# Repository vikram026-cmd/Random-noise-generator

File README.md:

# Random Noise Generator

## Overview
This project presents the design and implementation of a **Random Noise Generator**. The circuit was first simulated using LTspice to analyze noise behavior, and then implemented as a **2-layer PCB using KiCad**.

The project demonstrates the complete workflow from simulation to hardware design.

---

## Features
- Generation of random noise signals  
- Simulation of white noise and pink noise  
- Frequency behavior analysis  
- 2-layer PCB design  
- Compact and practical layout  

---

## Tools Used
- **LTspice** – Circuit simulation  
- **KiCad** – Schematic and PCB design  

---

## Project Workflow

### 1. LTspice Simulation
- Designed and simulated the circuit  
- Observed random signal behavior  
- Verified noise characteristics  

### 2. PCB Design (KiCad)
- Recreated schematic in KiCad  
- Designed a 2-layer PCB  
- Optimized component placement and routing  

---

## Results
- Successfully generated random noise signals in simulation  
- Verified expected noise behavior  
- Designed a functional 2-layer PCB  
- Layout is ready for fabrication  

---

## Applications
- Electronic system testing  
- Audio signal generation  
- Communication systems  

---

## Future Improvements
- Hardware fabrication and testing  
- Adjustable noise control  
- Signal filtering enhancements  

---

## Reference
R. L. Boylestad and L. Nashelsky, *Electronic Devices and Circuit Theory*, 11th ed., Pearson, 2013.

---

## Author
**THANGAVIKRAMAN RAMACHANDRAN**  
B.E. Electronics and Communication Engineering (Pre-Final Year)  

🔗 LinkedIn: https://www.linkedin.com/in/thangavikraman-ramachandran/

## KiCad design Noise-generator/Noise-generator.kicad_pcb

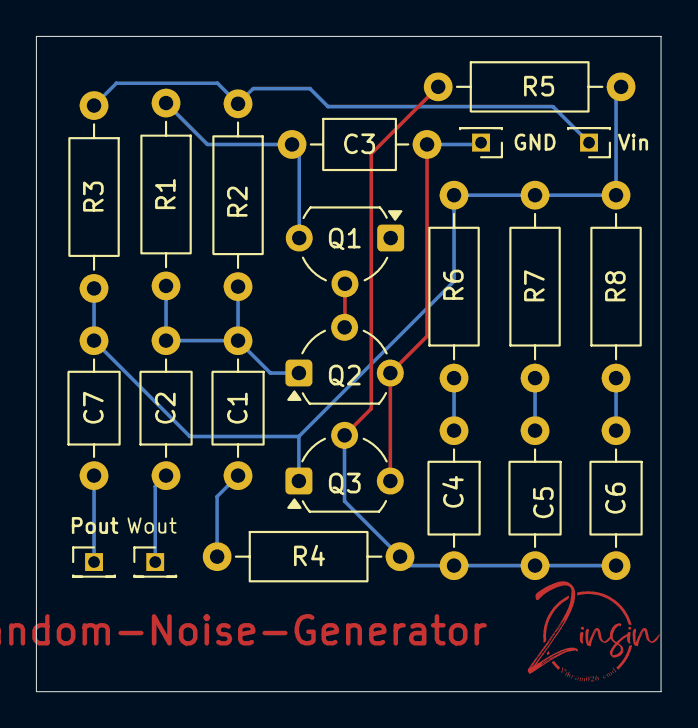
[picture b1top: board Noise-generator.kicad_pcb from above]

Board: 2 copper layers, 34.7 x 36.4 mm, 22 parts (0 on the bottom side), 13 nets.

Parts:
C1, C2, C3, C4, C5, C6, C7: C; C_Axial_L3.8mm_D2.6mm_P7.50mm_Horizontal
GND: TestPoint; PinHeader_1x01_P1.27mm_Vertical
Pout: TestPoint; PinHeader_1x01_P1.27mm_Vertical
Q1, Q2, Q3: NPN; TO-92L_Wide
R1, R2, R3, R4, R5, R6, R7, R8: R; R_Axial_DIN0207_L6.3mm_D2.5mm_P10.16mm_Horizontal
Vin: TestPoint; PinHeader_1x01_P1.27mm_Vertical
Wout: TestPoint; PinHeader_1x01_P1.27mm_Vertical

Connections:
/Q1-B: Q1.2 (B), Q2.2 (B)
/Q1-E: C3.1, Q1.3 (E), R1.1
/Q2-C: C1.1, C2.2, Q2.1 (C), R1.2, R2.2
/Q3-B: C4.2, C5.2, C6.2, Q3.2 (B), R4.2, R5.1
/Q3-C: C7.2, Q3.1 (C), R3.2, R5.2, R6.2, R7.2, R8.2
/c1-r4: C1.2, R4.1
/p-out: C7.1, Pout.1
/r6-c4: C4.1, R6.1
/r7-c5: C5.1, R7.1
/r8-c6: C6.1, R8.1
/w-out: C2.1, Wout.1
GND: C3.2, GND.1, Q2.3 (E), Q3.3 (E)
VCC: R2.1, R3.1, Vin.1

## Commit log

2026-03-28 version 1.0
2026-03-28 version 1.0
    Added detailed project overview, features, tools used, workflow, results, applications, future improvements, and author information.
2026-03-28 version 1.0
    Removed images and sections related to circuit diagrams and output waveforms. Updated author name and LinkedIn link.
